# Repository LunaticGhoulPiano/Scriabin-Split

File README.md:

# Scriabin-Split
My first ergo split keyboard.
Alexander Nikolayevich Scriabin (Александр Николаевич Скрябин) is a pianist famous for his small hands. This project use his name as a reference of my basic requirement of my own keyboard.

## STILL IN PROGRESS!!!

## Warning
1. Current works are all working on [Official WebGUI](https://ergogen.ceoloide.com/). If you want to run locally, make sure you know how to configure footprints and the pcb block.
2. Can't define footprints for dynamical usage, even on [Ceoloide's WebGUI](https://ergogen.ceoloide.com/):
    - No errors and workable, but not dynamic and stupid:
        ```yaml
        meta:
            engine: 4.2.1
            # code ...
            switch_settings:
                # code ...
        units:
            $extends: meta.switch_settings.mx
        # code ...
        pcbs:
            left:
                template: kicad8
                outlines:
                main:
                    outline: plate_left
                footprints:
                mcu:
                    what: ceoloide/mcu_supermini_nrf52840 # <===== directly set here
                    where: 
                    ref: controller_left_board_r0 
                    params:
                    P1: C0
                    P0: C1
                    P2: C2
                    P3: C3
                    P4: C4
                    P5: C5
                    P6: C6
                    P7: C7
                    P21: R0
                    P20: R1
                    P19: R2
                    P18: R3
                    P15: R4
                    P14: R5
                choc_switches:
                    what: ceoloide/switch_mx # <===== directly set here
                    where: /^left.*/
                    params:
                    from: "{{column_net}}"
                    to: "{{row_net}}"
                diodes:
                    what: ceoloide/diode_tht_sod123 # <===== directly set here
                    where: /^left.*/
                    params:
                    from: "{{column_net}}"
                    to: "{{row_net}}"
                    adjust:
                    shift: [0, -5]
            right:
                # code ...
        ```
    - Error:
        ```yaml
        # presets
        meta:
            engine: 4.2.1
            # code ...
            footprint_settings: # define here is OK
                v1:
                mcu_footprint: ceoloide/mcu_supermini_nrf52840
                switch_footprint: ceoloide/switch_mx
                diode_footprint: ceoloide/diode_tht_sod123
            switch_settings:
                # code ...
        units:
            $extends: [meta.switch_settings.mx, meta.footprint_settings.v1] # but once footprint_settings got extended will get: "Error: Undefined symbol ceoloide"
        # code ...
        pcbs:
            left:
                template: kicad8
                outlines:
                main:
                    outline: plate_left
                footprints:
                mcu:
                    what: mcu_footprint # <===== I wanna write in this way
                    where: 
                    ref: controller_left_board_r0 
                    params:
                    P1: C0
                    P0: C1
                    P2: C2
                    P3: C3
                    P4: C4
                    P5: C5
                    P6: C6
                    P7: C7
                    P21: R0
                    P20: R1
                    P19: R2
                    P18: R3
                    P15: R4
                    P14: R5
                choc_switches:
                    what: switch_footprint # <===== I wanna write in this way
                    where: /^left.*/
                    params:
                    from: "{{column_net}}"
                    to: "{{row_net}}"
                diodes:
                    what: diode_footprint_ # <===== I wanna write in this way
                    where: /^left.*/
                    params:
                    from: "{{column_net}}"
                    to: "{{row_net}}"
                    adjust:
                    shift: [0, -5]
            right:
                # code ...
        ```

## Tools
- [Ergogen](https://github.com/ergogen/ergogen)
- [OpenSCAD](https://openscad.org/)
- [Kicad](https://www.kicad.org/)

## References
### Ergogen
- [Official documents](https://docs.ergogen.xyz/)
- [FlatFootFox's step-by-step tutorial](https://flatfootfox.com/ergogen-introduction/)
- [Ben Vallack's video tutorial](https://youtu.be/M_VuXVErD6E)
### QMK
- [ZiTe (SideraKB) - DIY a QMK Keyboard (Traditional Chinese)](https://blog.ziteh.dev/categories/%E8%87%AA%E8%A3%BDqmk%E9%8D%B5%E7%9B%A4)

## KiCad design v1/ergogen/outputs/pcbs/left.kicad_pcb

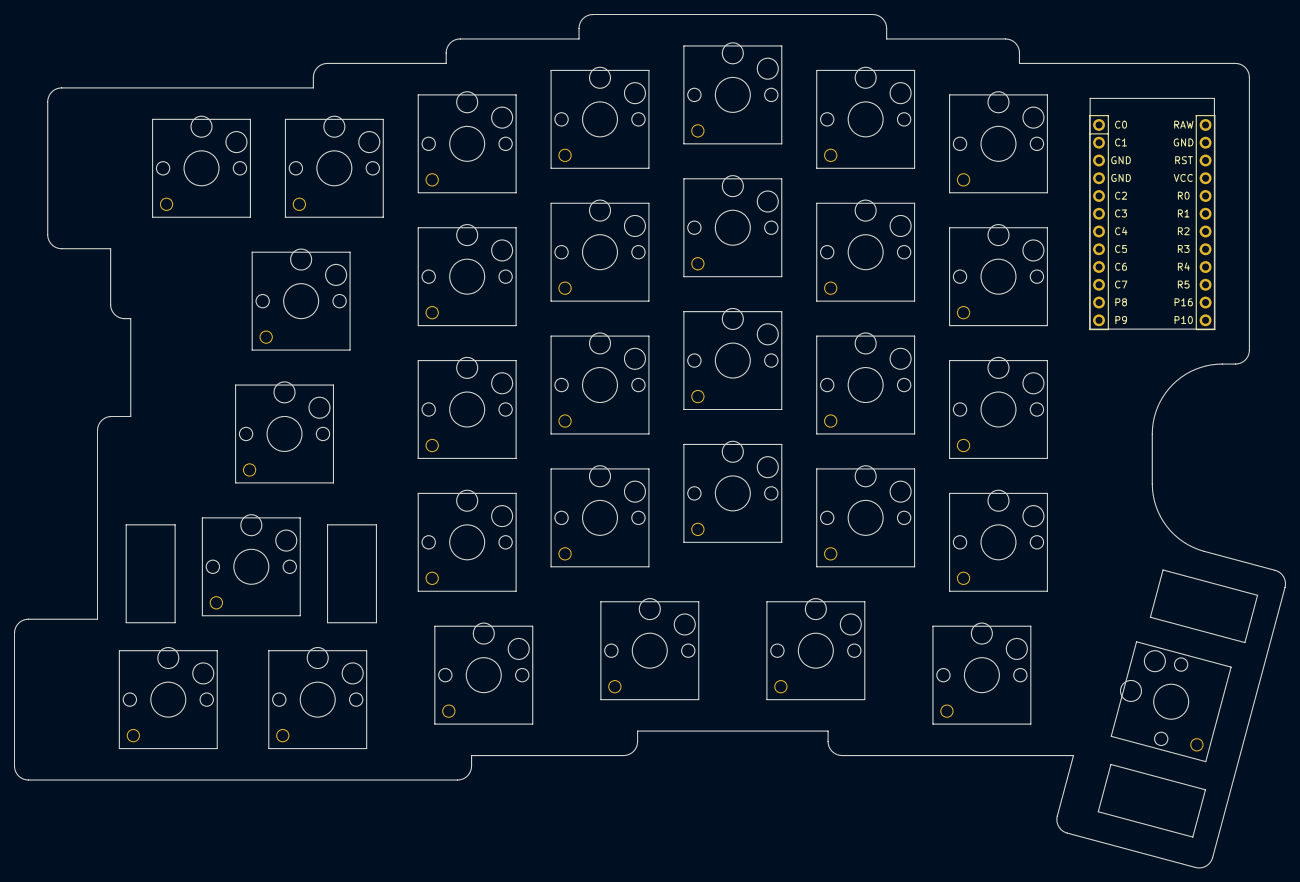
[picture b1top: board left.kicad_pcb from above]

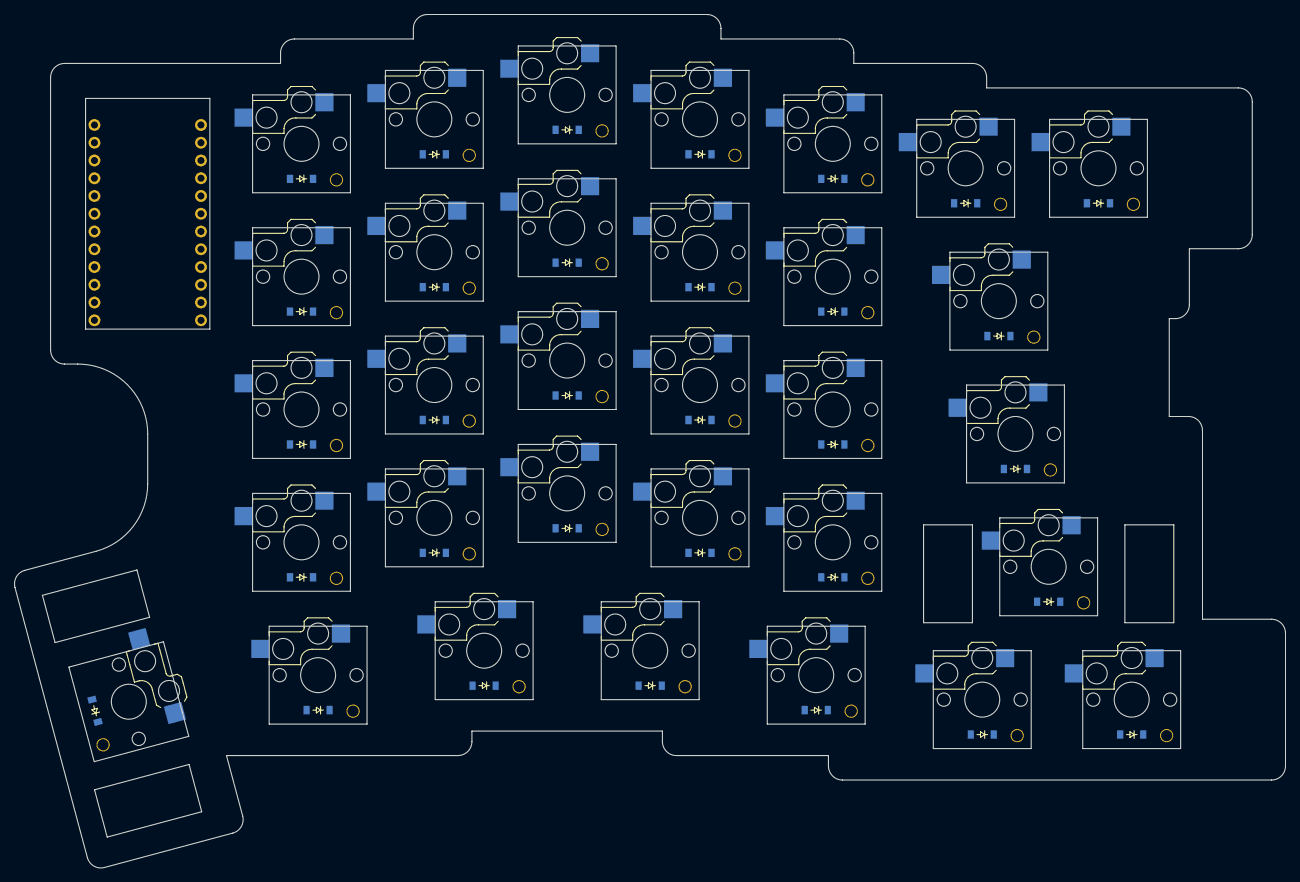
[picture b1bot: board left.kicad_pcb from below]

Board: 2 copper layers, 181.8 x 122.1 mm, 65 parts (64 on the bottom side), 13 nets, no tracks yet.

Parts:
D1, D2, D3, D4, D5, D6, D7, D8, D9, D10, D11, D12, D13, D14, D15, D16, D17, D18, D19, D20, D21, D22, D23, D24, D25, D26, D27, D28, D29, D30, D31, D32: diode_tht_sod123
MCU1: mcu_supermini_nrf52840
S1, S2, S3, S4, S5, S6, S7, S8, S9, S10, S11, S12, S13, S14, S15, S16, S17, S18, S19, S20, S21, S22, S23, S24, S25, S26, S27, S28, S29, S30, S31, S32: switch_choc_v1_v2

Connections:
C0: D1.2, D26.2, MCU1.24, S1.1, S26.1
C1: D2.2, D3.2, D4.2, D5.2, D27.2, MCU1.23, S2.1, S3.1, S4.1, S5.1, S27.1
C2: D6.2, D7.2, D8.2, D9.2, D28.2, MCU1.20, S6.1, S7.1, S8.1, S9.1, S28.1
C3: D10.2, D11.2, D12.2, D13.2, D29.2, MCU1.19, S10.1, S11.1, S12.1, S13.1, S29.1
C4: D14.2, D15.2, D16.2, D17.2, D30.2, MCU1.18, S14.1, S15.1, S16.1, S17.1, S30.1
C5: D18.2, D19.2, D20.2, D21.2, D31.2, MCU1.17, S18.1, S19.1, S20.1, S21.1, S31.1
C6: D22.2, D23.2, D24.2, D25.2, D32.2, MCU1.16, S22.1, S23.1, S24.1, S25.1, S32.1
GND: MCU1.2, MCU1.21, MCU1.22
R0: D1.1, D5.1, D9.1, D13.1, D17.1, D21.1, D25.1, MCU1.5, S1.2, S5.2, S9.2, S13.2, S17.2, S21.2, S25.2
R1: D4.1, D8.1, D12.1, D16.1, D20.1, D24.1, MCU1.6, S4.2, S8.2, S12.2, S16.2, S20.2, S24.2
R2: D3.1, D7.1, D11.1, D15.1, D19.1, D23.1, MCU1.7, S3.2, S7.2, S11.2, S15.2, S19.2, S23.2
R3: D2.1, D6.1, D10.1, D14.1, D18.1, D22.1, MCU1.8, S2.2, S6.2, S10.2, S14.2, S18.2, S22.2
R4: D26.1, D32.1, MCU1.9, S26.2, S32.2

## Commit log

2026-02-05 Update very first version, finish outlines.
2026-02-06 Add controllers, adjust outlines.
2026-02-06 Add PCB template by Gemini, ProMicro nRF52840.
2026-02-06 Cleanup: remove footprint submodule and fix config
2026-02-06 Add web version of pcb settings
2026-02-06 Adjust the space between two boards in Kicad A4 blueprint.
2026-02-06 Append files download from ceoloide's website.
2026-02-07 Change to ceoloide mx
2026-02-07 Update status
2026-02-07 Move settings into meta, edit README
